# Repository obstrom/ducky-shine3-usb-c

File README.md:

# Ducky Shine3 USB-C Mod

Unofficial USB 2.0 Type C replacement module for the Ducky Shine3 (DK9008S3) mechanical keyboard first released in 2013.

This module is ment to replace the original USB 2.0 mini port on the Ducky Shine3, making it compatible with any USB C data cable.

The project includes KiCad files. Feel free to edit and modify to your own needs. This also includes the gerber files if you want to order this PCB without doing any modifications. I've had one successful order of this PCB from JLCPCB without any issues.

To install this module you will have to slightly enlarge the USB connector opening in the hard plastic shell of the keyboard. I did this using my soldering iron and then tidied it up with a small file.

## KiCad

External footprint
* USB-C Connector: [USB4105-GF-A-060](https://www.snapeda.com/parts/USB4105-GF-A-060/GCT/view-part)

## PCB Specifications
| Specification | Value            |
| ------------- | ---------------- |
| Dimensions    | 50 x 18 mm       |
| Thickness     | 1 mm             |
| Layers        | 2                |
| Copper        | 1 oz (35μm)      |
| Via covering  | Tented or filled |

## Parts
Parts needed to assemble the PCB.
| Amount | Part type                    | Part name                                                                     |
| ------ | ---------------------------- | ----------------------------------------------------------------------------- |
| 1      | USB2.0 Type C 16+8 connector | [USB4105-GF-A-060](https://www.digikey.se/sv/products/detail/gct/USB4105-GF-A-060/14559036) |
| 1      | 1x5 right angle connector    | [2PH1R-05-UAA](https://www.digikey.se/en/products/detail/adam-tech/2PH1R-05-UA/9830981) |
| 2      | 5.1 kOhms resistor           | [RNMF14FTC5K10](https://www.digikey.se/en/products/detail/stackpole-electronics-inc/RNMF14FTC5K10/2617363) |

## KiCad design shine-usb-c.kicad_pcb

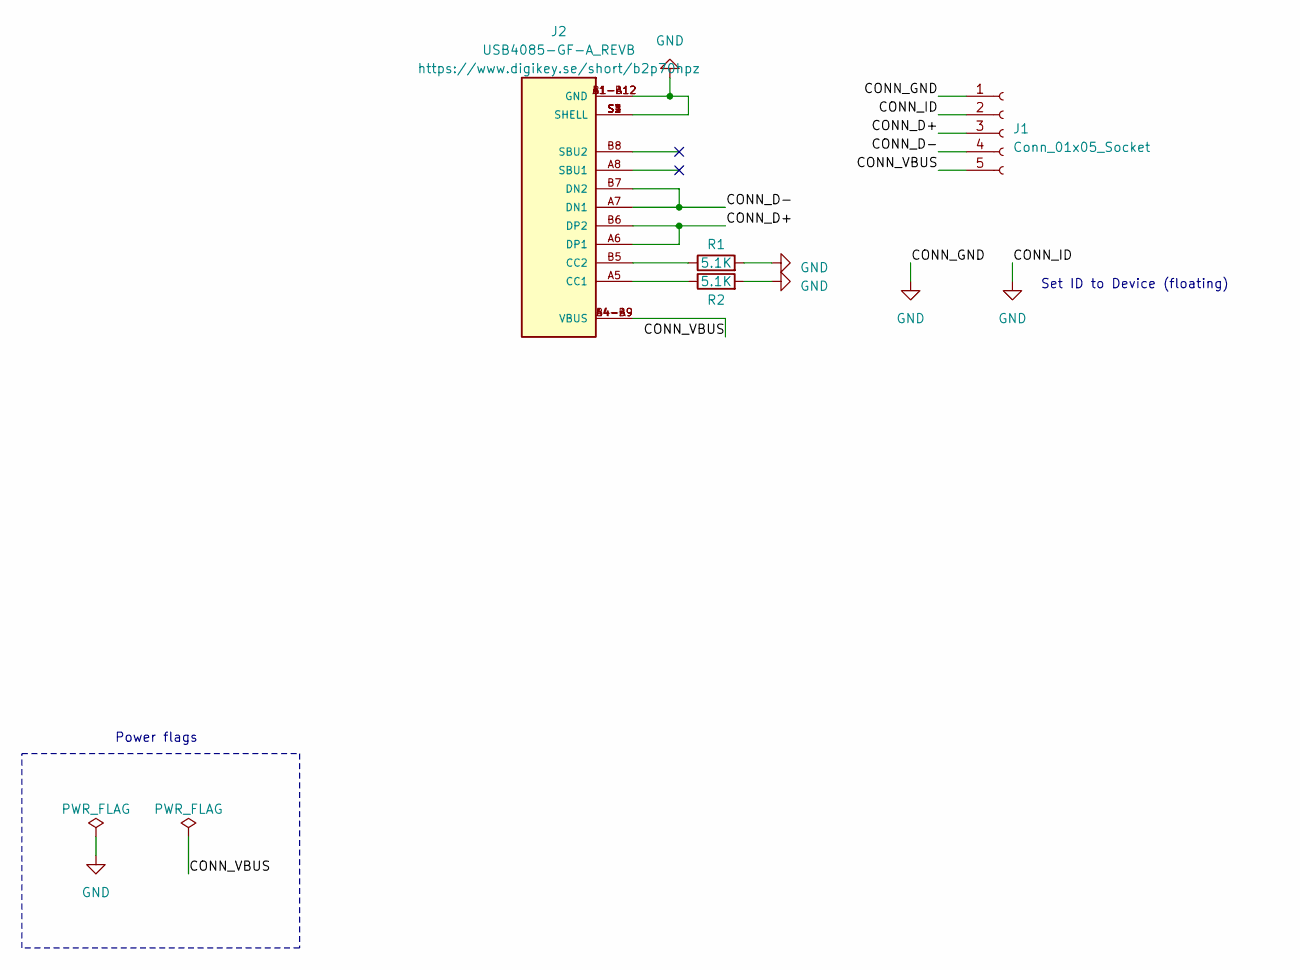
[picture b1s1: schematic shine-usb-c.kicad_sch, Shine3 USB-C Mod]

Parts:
J1: Conn_01x05_Socket; PinHeader_1x05_P2.00mm_Vertical
J2: USB4085-GF-A_REVB; USB4105-GF-A-060-MFG; PARTREV B
R1, R2: 5.1K; R_Axial_DIN0204_L3.6mm_D1.6mm_P7.62mm_Horizontal

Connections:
/CONN_D+: J1.3, J2.A6 (DP1), J2.B6 (DP2)
/CONN_D-: J1.4, J2.A7 (DN1), J2.B7 (DN2)
/CONN_VBUS: J1.5, J2.A4-B9 (VBUS), J2.B4-A9 (VBUS)
GND: J1.1, J1.2, J2.A1-B12 (GND), J2.B1-A12 (GND), J2.S1 (SHELL), J2.S2 (SHELL), J2.S3 (SHELL), J2.S4 (SHELL), R1.2, R2.2
unnamed: J2.A5 (CC1), R2.1
unnamed: J2.B5 (CC2), R1.1

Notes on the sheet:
Set ID to Device (floating)
Power flags

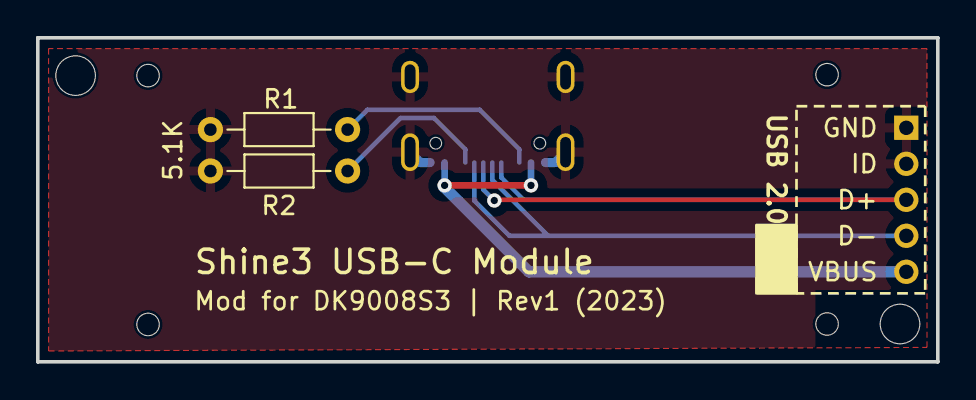
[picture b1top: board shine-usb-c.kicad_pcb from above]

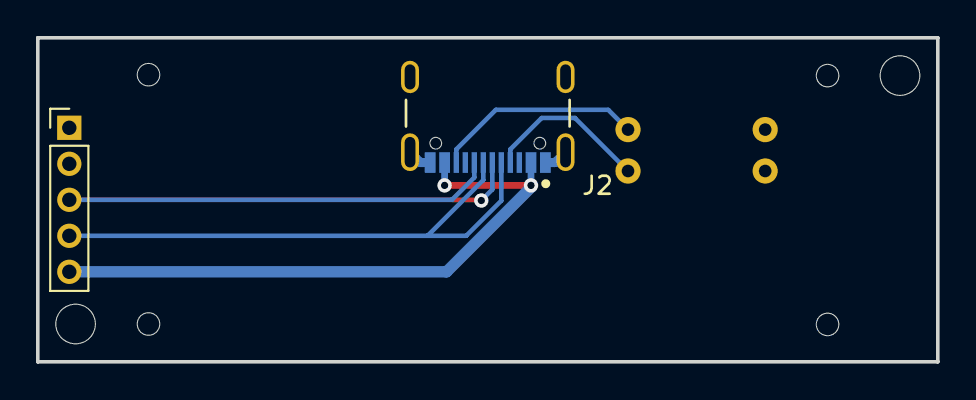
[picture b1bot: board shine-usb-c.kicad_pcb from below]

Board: 2 copper layers, 50.0 x 18.0 mm, 4 parts (2 on the bottom side), 6 nets.

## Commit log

2023-10-29 Add KiCad files
2023-10-29 Add gerber files
2023-10-29 Fix README
2023-10-29 Gitignore
2026-03-22 Update USB-C component name
    Fixed reference to incorrect USB-C component version
